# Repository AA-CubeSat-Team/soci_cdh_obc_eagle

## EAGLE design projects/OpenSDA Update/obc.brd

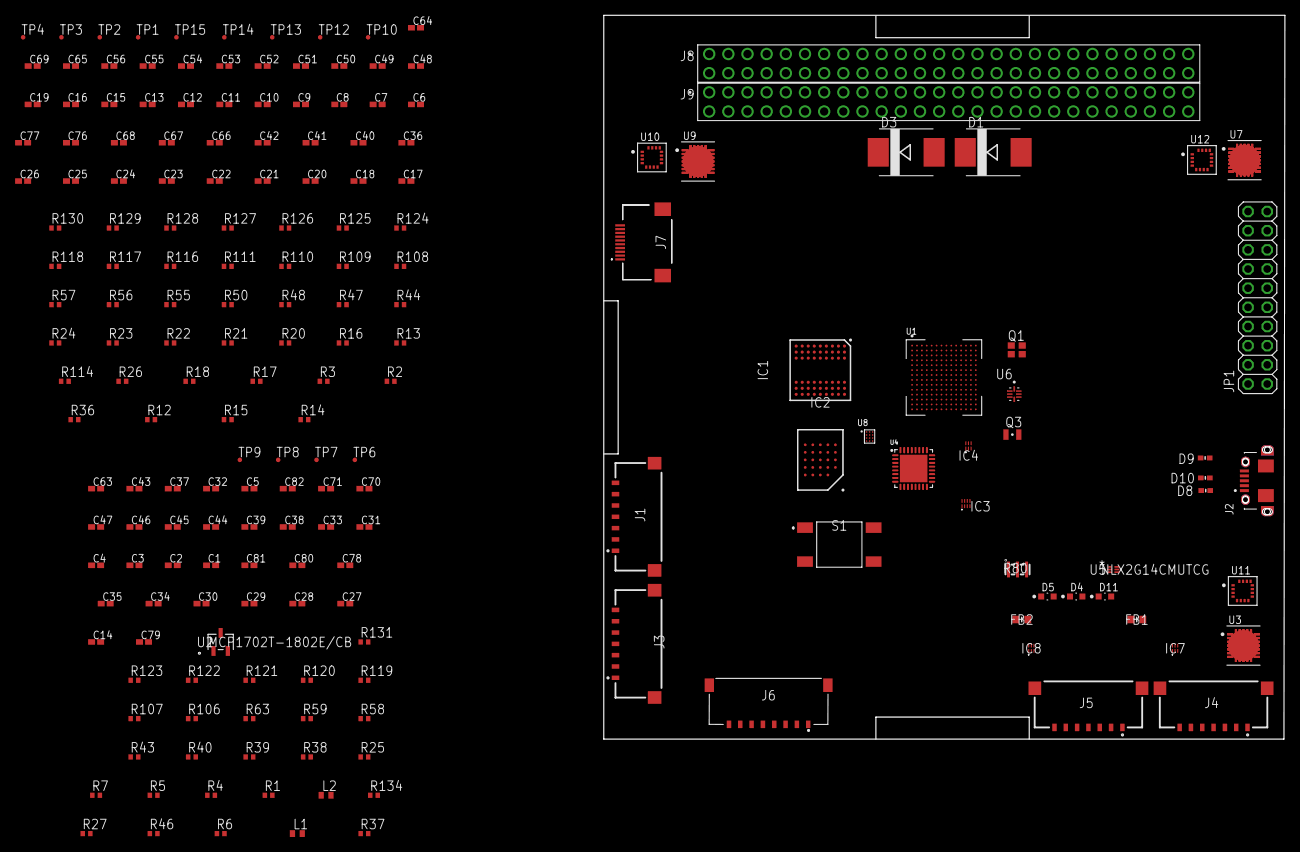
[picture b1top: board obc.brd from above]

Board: 2 copper layers, 90.3 x 95.9 mm, 192 parts (0 on the bottom side), 169 nets, no tracks yet.

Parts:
C1, C2, C4, C7, C8, C9, C10, C11, C12, C13, C38, C44, C45, C46, C47, C50, C51, C56: 0.1uF; C0402K
C3, C6, C16, C19, C31, C33, C39, C48, C49, C52, C53, C54, C55: 4.7uF; C0402K
C5: 22uF; C0402K
C14, C17, C18, C20, C21, C22, C23, C24, C25, C26, C27, C28, C29, C30, C34, C35, C36, C40, C41, C42: 0.22uF; C0402K
C15: 1.0uF; C0402K
C32, C43: 10uF; C0402K
C37: 33uF; C0402K
C63, C64: 18pF; C0402K
C65, C69, C82: 10 uF; C0402K
C66: 2.2 uF; C0402K
C67, C76, C77, C78, C81: 0.1 uF; C0402K
C68: 1.0 uF; C0402K
C70, C71: 22 pF; C0402K
C79: 1000 pF; C0402K
C80: 4.7 uF; C0402K
D1, D3: SMC
D4, D5, D11: KINGBRIGHT_KPT-1608SGCKINGBRIGHT_KPT-1608SGC_0_0; KINGBRIGHT_KPT-1608SGC_0
D8, D9, D10: 0402ESDA-MLP1; DIONC1105X44N
FB1, FB2: MPZ1608S331A; BEADC1608X95N
IC1: IS42S16160J-6BLI; BGA54C80P9X9_800X800X120
IC2: S26KS512SDPBHI020; BGA24C100P5X5_600X800X100
IC3: 74LVC2T45GS,115; 74AXP2T3407GSX
IC4, IC7, IC8: 74LVCH1T45GS,132; 74LVC1G3157GS132
J1, J3, J4, J5: 504050-0791
J2: DX4R205JJAR1800; JAE_DX4R205JJAR1800
J6: 504050-0891; 5040500891
J7: FH28-10S-0.5SH_05_; FH2810S05SH05
J8, J9: ESQ-126-39-G-D; SAMTEC_ESQ-126-39-G-D
JP1: 2X10
L1: 120 Ohm; 0402
L2: 4.7 uH; 0402
Q1: FA-128
Q3: FC-12M
R1, R4, R5, R7, R13, R16, R20, R21, R22, R23, R24, R25, R38, R39, R40, R43, R44, R47, R48, R50, R55, R56, R57, R58, R59, R63, R106, R107, R108, R109, R110, R111, R116, R117, R118, R119, R120, R121, R122, R123, R124, R125, R126, R127, R128, R129, R130, R131: 0 Ohm; R0402
R2, R3, R17, R18, R26: 10k Ohm; R0402
R6: 30K Ohm; R0402
R12: 2.2M Ohm; R0402
R14, R15: 100K Ohm; R0402
R27: 100 Ohm; R0402
R36, R37: 4.7K Ohm; R0402
R46: 10K Ohm; R0402
R80: CSTCE8M00G55-R0; CSTCE12M0G55-R0
R114, R134: 1k Ohm; R0402
S1: TL3301AF260QG
TP1, TP2, TP3, TP4, TP6, TP7, TP8, TP9, TP10, TP12, TP13, TP14, TP15: TPTP06R; TP06R
U1: MIMXRT1052DVL6A; BGA196C65P14X14_1000X1000X152N
U2: MCP1702T-1802E/CB; SOT-23A_MC
U3, U7, U9: NXP_FXAS21002CQR1NXP_FXAS21002CQR1_0_0; NXP_FXAS21002CQR1_0
U4: MK20DX128VFM5; QFN50P500X500X100-33N
U5: NLX2G14CMUTCG; UDFN6_1X1
U6: NTSX2102GU8H; QFN40P140X120X50-8N
U8: NX5P3090UKZ; BGA12CP40_3X4_135X165X56B26N
U10, U11, U12: HONEYWELL_HMC5983-TRHONEYWELL_HMC5983-TR_0_0; HONEYWELL_HMC5983-TR_0

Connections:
1_RSVD_GND: U3.6, U7.6, U9.6
2_RSVD_GND: U3.7, U7.7, U9.7
3_RSVD_GND: U3.9, U7.9, U9.9
4_RSVD_GND: U3.10, U7.10, U9.10
5_RSVD_GND: U3.20, U7.20, U9.20
6_RSVD_GND: U3.21, U7.21, U9.21
7_RSVD_GND: U3.22, U7.22, U9.22
8_RSVD_GND: U3.23, U7.23, U9.23
9_RSVD_GND: U3.24, U7.24, U9.24
CAN_STBY: R44.2, U1.G14
DCDC_3V3: C1.1, C2.1, C3.1, C14.1, C15.1, C18.1, C19.1, D1.A, L1.1, R1.2, R7.2, R27.1, R63.2, R114.2, R134.2, U1.E6, U1.F5, U1.N14, U1.P12
DCDC_OUT: C36.1, C37.1, L2.2, R5.2
FLASH_VCC: C51.1, C52.1, C55.1, C56.1, IC2.B4, IC2.D1, IC2.E4, R2.1, R3.1, R4.2, R17.1, R18.1, U1.K5
FLEXSPI_CLK: R22.1, U1.L4
FLEXSPI_CLK_B: IC2.B1, U1.P2
FLEXSPI_D0_A: R24.2, U1.P3
FLEXSPI_D0_B: IC2.D5, U1.M4
FLEXSPI_D1_A: R23.2, U1.N4
FLEXSPI_D1_B: IC2.E3, U1.M3
FLEXSPI_D2_A: R16.2, U1.P4
FLEXSPI_D2_B: IC2.E2, U1.M5
FLEXSPI_D3_A: R25.2, U1.P5
FLEXSPI_D3_B: IC2.E1, U1.L5
FLEXSPI_DQS: R21.1, U1.N3
FLEXSPI_SS0: R20.1, U1.L3
GND: C1.2, C2.2, C3.2, C4.2, C5.2, C6.2, C7.2, C8.2, C9.2, C10.2, C11.2, C12.2, C13.2, C14.2, C15.2, C16.2, C17.2, C18.2, C19.2, C20.2, C21.2, C22.2, C23.2, C24.2, C25.2, C26.2, C27.2, C28.2, C29.2, C30.2, C31.2, C32.2, C33.2, C34.2, C35.2, C36.2, C37.2, C38.2, C39.2, C40.2, C41.2, C42.2, C43.2, C44.2, C45.2, C46.2, C47.2, C48.2, C49.2, C50.2, C51.2, C52.2, C53.2, C54.2, C55.2, C56.2, C63.1, C64.1, C65.2, C66.2, C67.2, C68.2, C69.2, C70.2, C71.2, C76.2, C77.2, C78.2, C79.2, C80.2, C81.2, C82.2, D5.1, D8.1, D9.1, D10.1, FB2.1, IC1.A1, IC1.A3, IC1.B7, IC1.C3, IC1.D7, IC1.E3, IC1.J1, IC2.B3, IC2.B5, IC2.C1, IC2.C5, IC2.E5, IC3.4, IC3.5, IC4.2, IC7.2, IC8.2, J2.5, JP1.4, JP1.6, JP1.8, JP1.10, JP1.12, JP1.14, JP1.16, JP1.18, JP1.20, Q1.2, Q1.4, R12.1, R14.1, R26.1, R46.1, R80.2, S1.1, S1.3, U1.A1, U1.A14, U1.B5, U1.B10, U1.E2, U1.E13, U1.G7, U1.G8, U1.H7, U1.H8, U1.J7, U1.J8, U1.K2, U1.K6, U1.K9, U1.K13, U1.L9, U1.N1, U1.N2, U1.N5, U1.N8, U1.P1, U1.P14, U2.1, U4.2, U4.8, U4.33, U5.2, U6.4, U8.B3, U8.C3, U8.D3
GND1: U3.1, U7.1, U9.1
GND2: U3.5, U7.5, U9.5
GND3: U3.14, U7.14, U9.14
GND4: U3.19, U7.19, U9.19
GPIO_AD_B0_00: R38.1, R131.1
GPIO_AD_B0_01: R39.1, R130.1
GPIO_AD_B0_02: R125.1, U1.M11
GPIO_AD_B0_03: R43.1, R124.1
GPIO_AD_B0_09: R55.1, R120.1
GPIO_AD_B0_10: R56.1, R121.1
GPIO_AD_B0_11: R57.1, R118.1
GPIO_AD_B1_00: R58.2, R111.1, U1.J11
GPIO_AD_B1_01: R59.2, R110.1, U1.K11
GPIO_AD_B1_02: R122.1, U1.L11
GPIO_AD_B1_03: R123.1, U1.M12
GPIO_AD_B1_04: R108.1, U1.L12
GPIO_AD_B1_05: R109.1, U1.K12
GPIO_AD_B1_06: R117.1, U1.J12
GPIO_AD_B1_07: R116.1, U1.K10
GPIO_AD_B1_08: R119.1, U1.H13
GPIO_AD_B1_10: R106.1, U1.L13
GPIO_AD_B1_11: R107.1, U1.J13
GPIO_SD_B0_00: R129.1, U1.J4
GPIO_SD_B0_01: R126.1, U1.J3
GPIO_SD_B0_02: R127.1, U1.J1
GPIO_SD_B0_03: R128.1, U1.K1
JTAG_MOD: R46.2, TP6.TP, U1.F13
JTAG_NTRST: JP1.3, R57.2, U1.G10
JTAG_TCK: JP1.9, R48.2, U1.F12
JTAG_TDI: JP1.5, R50.2, R55.2, U1.F14
JTAG_TDO: JP1.13, R56.2, U1.G13
JTAG_TMS: JP1.7, R47.2, U1.E14
LDO_1V8: C49.1, C50.1, R4.1, TP3.TP, U2.2
MCU_DCDC_IN: C39.1, C40.1, C41.1, C42.1, R6.2, R7.1, U1.K4, U1.L1, U1.L2
unnamed: C4.1, U1.B7
unnamed: C16.1, C17.1, U1.P8
unnamed: C20.1, U1.M10
unnamed: C35.1, R6.1, U1.K3
unnamed: C21.1, D1.C, U1.M9
unnamed: L2.1, U1.M1, U1.M2
unnamed: C33.1, C34.1, U1.P10
unnamed: IC2.A2, R17.2
unnamed: TP1.TP, U1.N10
unnamed: C54.1, Q1.3, R12.2, U1.P11
unnamed: C53.1, Q1.1, U1.N11
unnamed: IC1.F3, R14.2
unnamed: IC1.F2, R13.2
unnamed: IC1.G9, R15.1
unnamed: IC2.C4, R16.1
unnamed: IC2.A5, R18.2
unnamed: IC1.A7, IC1.A9, IC1.B3, IC1.C7, IC1.D3
unnamed: IC2.A4, R2.2
unnamed: IC2.C2, R3.2, R20.2
unnamed: IC2.C3, R21.2
unnamed: IC2.D2, R23.1
unnamed: IC2.B2, R22.2
unnamed: IC2.D3, R24.1
unnamed: IC2.D4, R25.1
unnamed: JP1.19, R26.2
unnamed: JP1.1, JP1.2, R27.2
unnamed: D3.C, JP1.15
unnamed: C32.1, C38.1, R1.1, U2.3
unnamed: C63.2, Q3.2, U1.N9
unnamed: C64.2, Q3.1, U1.P9
unnamed: TP12.TP, U6.3
unnamed: TP13.TP, U6.6
unnamed: D5.2, R114.1
unnamed: D11.2, R134.1
NVCC_GPIO_3V3: C45.1, C46.1, C47.1, C48.1, R36.2, R37.2, R63.1, U1.E9, U1.F10, U1.J10
ONOFF: TP2.TP, U1.M6
P3V3_SDA: C67.1, C68.1, C69.1, C76.1, C78.1, IC3.1, IC4.1, IC7.1, IC8.1, U4.1, U4.7, U4.11, U5.5, U6.1
P5V0_SDA_USB_CONN_VBUS: D8.2, FB1.1, J2.1
P5V_SDA: C65.1, C81.1, C82.1, FB1.2, U4.6, U8.B1, U8.B2, U8.C1
P5V_SDA_S: C80.1, U8.C2, U8.D1, U8.D2
POR_B: D3.A, R40.2, U1.M7
RST_TGTMCU_B: C79.1, R40.1, S1.2, S1.4, U6.2, U6.7
SDA_EXTAL: C70.1, R80.3, U4.17
SDA_LED: D4.1, U4.29
SDA_RST: TP7.TP, U4.19
SDA_SPI0_CS: TP15.TP, U4.23
SDA_SPI0_RST_B: TP14.TP, U4.22
SDA_SPI0_SCK: IC8.3, U4.26
SDA_SPI0_SIN: IC3.3, U4.28
SDA_SPI0_SOUT: IC7.3, U4.27
SDA_SWD_EN: IC8.5, U5.6
SDA_SWD_EN_B: U4.16, U5.1
SDA_SWD_OE: IC7.5, U5.4
SDA_SWD_OE_B: U4.20, U5.3
SDA_USBSHIELD: FB2.2, J2.S4, J2.S5
SDA_USB_CONN_DN: D10.2, J2.2
SDA_USB_CONN_DP: D9.2, J2.3
SDA_VOUT33: C66.1, U4.5
SDA_XTAL: C71.1, R80.1, U4.18
SDRAM_3V3: C5.1, C6.1, C7.1, C8.1, C9.1, C10.1, C11.1, C12.1, C13.1, L1.2
SEMC_A0: IC1.H7, U1.C2
SEMC_A1: IC1.H8, U1.G1
SEMC_A2: IC1.J8, U1.G3
SEMC_A3: IC1.J7, U1.H1
SEMC_A4: IC1.J3, U1.A6
SEMC_A5: IC1.J2, U1.B6
SEMC_A6: IC1.H3, U1.B1
SEMC_A7: IC1.H2, U1.A5
SEMC_A8: IC1.H1, U1.A4
SEMC_A9: IC1.G3, U1.B2
SEMC_A10: IC1.H9, U1.G2
SEMC_A11: IC1.G2, U1.B4
SEMC_A12: IC1.G1, U1.A3
SEMC_D0: IC1.A8, U1.E3
SEMC_D1: IC1.B9, U1.F3
SEMC_D2: IC1.B8, U1.F4
SEMC_D3: IC1.C9, U1.G4
SEMC_D4: IC1.C8, U1.F2
SEMC_D5: IC1.D9, U1.G5
SEMC_D6: IC1.D8, U1.H5
SEMC_D7: IC1.E9, U1.H4
SEMC_D8: IC1.E1, U1.C6
SEMC_D9: IC1.D2, U1.C5
SEMC_D10: IC1.D1, U1.D5
SEMC_D11: IC1.C2, U1.C4
SEMC_D12: IC1.C1, U1.D4
SEMC_D13: IC1.B2, U1.E5
SEMC_D14: IC1.B1, U1.C3
SEMC_D15: IC1.A2, U1.E4
SWD_CLK: IC8.4, R48.1
SWD_DIO: IC3.6, IC7.4, R47.1
TC_EXTAL_TP: TP8.TP, U4.10
TC_SDA_USB_ID_TP: J2.4, TP10.TP
TC_XTAL_TP: TP9.TP, U4.9
UART1_RXD: IC4.4, U1.L14
UART1_RX_TGTMCU_R: IC4.3, U4.25
UART1_TXD: IC3.7, U1.K14
UART1_TX_TGTMCU_R: IC3.2, U4.24
USB_HOST_OC: R37.1, R38.2, U1.M14
USB_OTG1_ID: R36.1, R39.2, U1.H10
USB_OTG1_OC: R43.2, U1.G11
USER_BUTTON: TP4.TP, U1.L6
USER_LED: D11.1, R50.1
VDD: U3.15, U7.15, U9.15
VDDIO: U3.18, U7.18, U9.18
VDD_SOC_IN: C22.1, C23.1, C24.1, C25.1, C26.1, C27.1, C28.1, C29.1, C30.1, C31.1, R5.1, U1.F6, U1.F7, U1.F8, U1.F9, U1.G6, U1.G9, U1.H6, U1.H9, U1.J5, U1.J9
VDD_USB_3V: C43.1, C44.1, U1.K8
VTRG_FAULT_B: U4.32, U8.A2
V_TGTMCU: C77.1, IC3.8, IC4.6, IC7.6, IC8.6, U6.8

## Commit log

2019-10-25 updated schematic in OBC2
2019-11-15 Add files via upload
    Things left:
    1.Connecting pins to PC104 Header
    2.Creating a power flow diagram to see which LDOs to include
    3.add LEDs and fuse map
2019-11-22 updated sheets for new modules
2020-02-01 with BOM
2020-02-22 new updated
2020-02-22 updated files
2020-04-16 updated schematic and layout of the OBC (with BOM)
2020-04-16 update libraries

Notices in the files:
parts and their libraries:
COPYRIGHT: Copyright (C) 2018 Accelerated Designs. All rights reserved
COPYRIGHT: Copyright (C) 2016 Accelerated Designs. All rights reserved
